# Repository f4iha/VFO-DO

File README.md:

# VFO-DO RF Generator

This VFO-DO is a HF generator covering from few kHz to 100MHz. This project provide to any beginner in electronic or radio the necessary elements to build a source of stable frequency (precise at the Herz level due to the steering by a GPS)... and it is very simple to build.

It is coming from the initial idea from Gene Marcus W3PM/GM4YRE and published in an [article](http://www.arrl.org/files/file/QEX_Next_Issue/2015/Jul-Aug_2015/Marcus.pdf) of QEX.
This repository is an evolution of the work done by F6ITU who provided a [KiCad project](https://github.com/F6ITU/VFO-DO/) for this VFO-DO.

This project can be used as field equipements, where it is unthinkable to move a served oscillator (fragile and expensive). This is mainly a simple approach to drive a little SDR or replace the VFO of a traditional radio device.

The cost of this is around 30 euros. However, please take in account the phase noise of this type of generator cannot compete with a traditional VFO-DO

## Specific features

During the integration, few changes were applied in the initial code of the author:
  * usage of a I2C Crystal Display, it is freeing multiple pin on the Arduino
  * add a button to disable the GPS at start

## Intellectual property and licence

The intellectual property and the publishing rights are owned respectively by the author and the publishing society mentioned.

Permission is granted to use, copy, modify, and distribute this firmware and documentation for non-commercial purposes.

## External links

More informations on the oscillator module based on SiLabs Si5351 : 
[https://learn.adafruit.com/adafruit-si5351-clock-generator-breakout?view=all](https://learn.adafruit.com/adafruit-si5351-clock-generator-breakout?view=all)

Another source for this module 
[https://www.sv1afn.com/si5351a.html](https://www.sv1afn.com/si5351a.html)
Careful : this last module is not "pin compatible" with the previous one

Origin firmware from the author [http://www.knology.net/~gmarcus/Si5351/Si5351_vfo_v5.ino.zip](http://www.knology.net/~gmarcus/Si5351/Si5351_vfo_v5.ino.zip)

A WSPR emitter-receiver designed by the author and using the VFO-DO
[http://www.knology.net/~gmarcus/Si5351/Si5351A_WSPR_XCVR.pdf](http://www.knology.net/~gmarcus/Si5351/Si5351A_WSPR_XCVR.pdf)

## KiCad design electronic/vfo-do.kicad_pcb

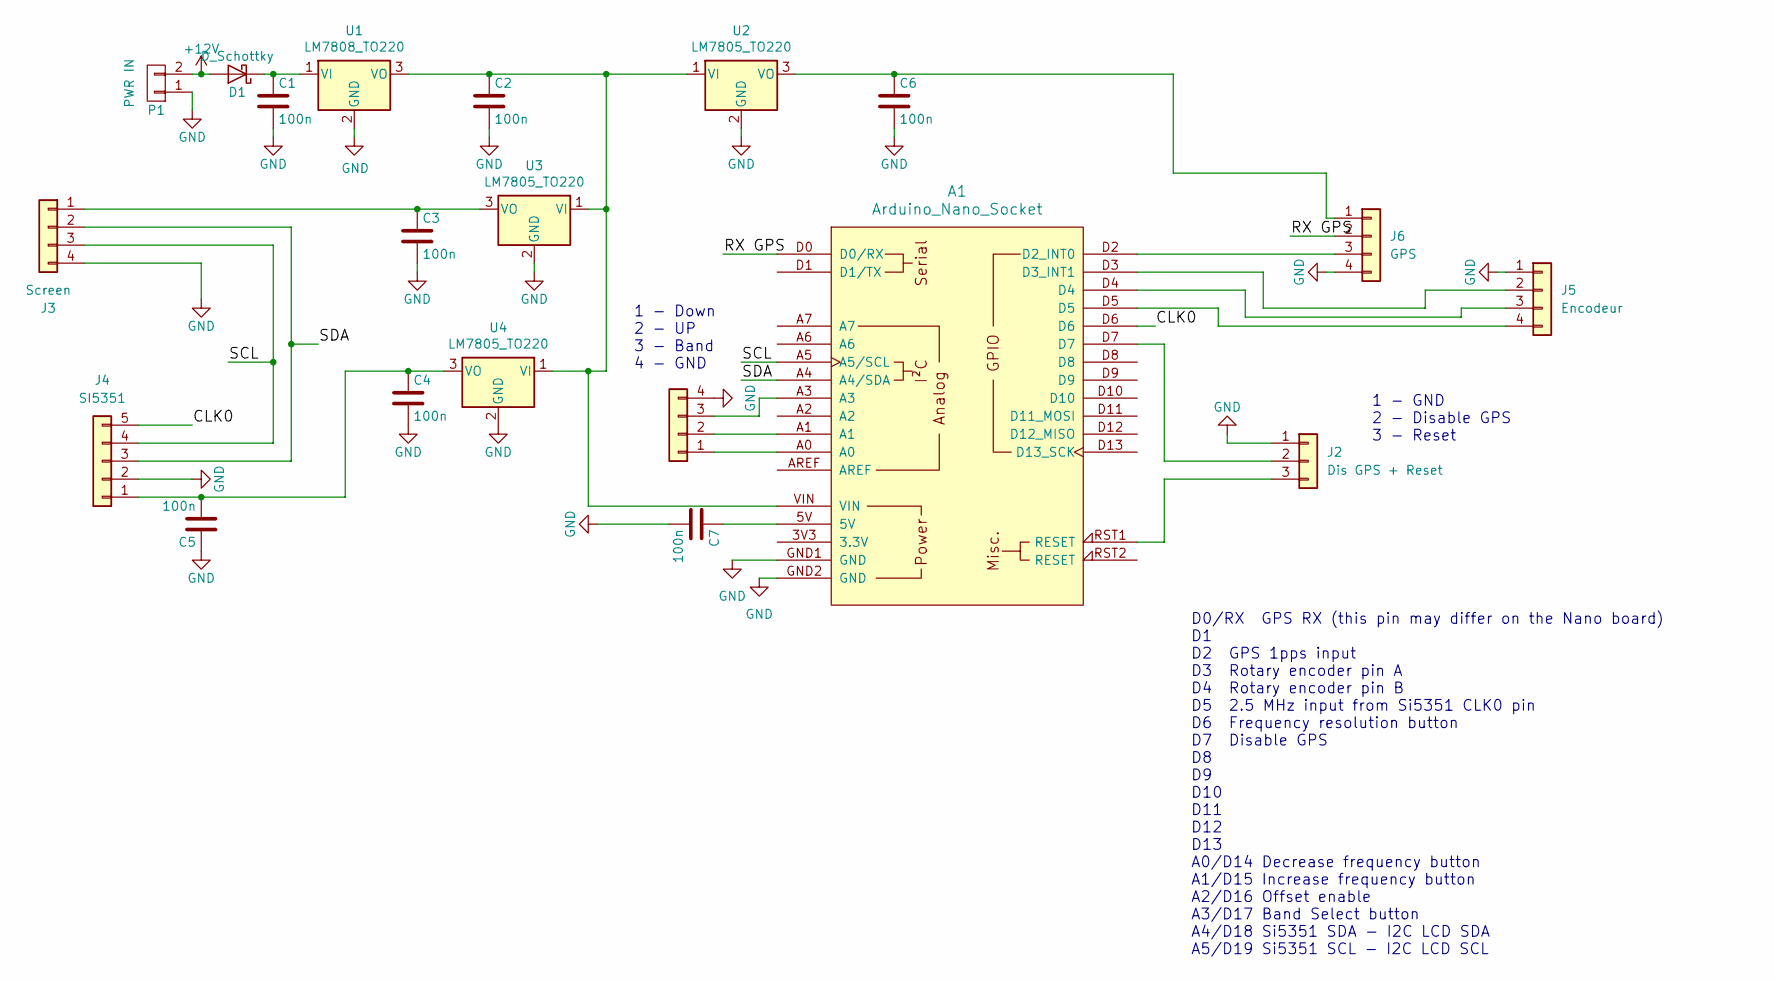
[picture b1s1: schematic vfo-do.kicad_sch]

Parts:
A1: Arduino_Nano_Socket
C1, C2, C3, C4, C5, C6, C7: 100n; C_Disc_D5.0mm_W2.5mm_P5.00mm
D1: D_Schottky; D_DO-41_SOD81_P7.62mm_Horizontal
J1: Commands; Molex_KK-254_AE-6410-04A_1x04_P2.54mm_Vertical
J2: Dis GPS + Reset; Molex_KK-254_AE-6410-03A_1x03_P2.54mm_Vertical
J3: Screen; Molex_KK-254_AE-6410-04A_1x04_P2.54mm_Vertical
J4: SI5351; Molex_KK-254_AE-6410-05A_1x05_P2.54mm_Vertical
J5: Encodeur; Molex_KK-254_AE-6410-04A_1x04_P2.54mm_Vertical
J6: GPS; Molex_KK-254_AE-6410-04A_1x04_P2.54mm_Vertical
P1: PWR IN; Molex_KK-254_AE-6410-02A_1x02_P2.54mm_Vertical
U1: LM7808_TO220; TO-220-3_Vertical
U2, U3, U4: LM7805_TO220; TO-220-3_Vertical

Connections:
+12V: D1.2 (A), P1.2
/CLK0: A1.D6, J4.5
/RX GPS: A1.D0 (D0/RX), J6.2
/SCL: A1.A5 (A5/SCL), J3.3, J4.4
/SDA: A1.A4 (A4/SDA), J3.2, J4.3
GND: A1.GND1 (GND), A1.GND2 (GND), C1.2, C2.2, C3.2, C4.2, C5.1, C6.2, C7.2, J1.4, J2.1, J3.4, J4.2, J5.1, J6.4, P1.1, U1.2 (GND), U2.2 (GND), U3.2 (GND), U4.2 (GND)
unnamed: A1.D2 (D2_INT0), J6.3
unnamed: A1.D3 (D3_INT1), J5.2
unnamed: A1.5V, C7.1
unnamed: C1.1, D1.1 (K), U1.1 (VI)
unnamed: A1.A0, J1.1
unnamed: A1.A1, J1.2
unnamed: A1.A3, J1.3
unnamed: A1.D7, J2.2
unnamed: A1.RST1 (RESET), J2.3
unnamed: C3.1, J3.1, U3.3 (VO)
unnamed: C4.1, C5.2, J4.1, U4.3 (VO)
unnamed: A1.D4, J5.3
unnamed: A1.D5, J5.4
unnamed: C6.1, J6.1, U2.3 (VO)
unnamed: A1.VIN, C2.1, U1.3 (VO), U2.1 (VI), U3.1 (VI), U4.1 (VI)

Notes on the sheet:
1 - Down 2 - UP 3 - Band 4 - GND
D0/RX GPS RX (this pin may differ on the Nano board) D1 D2 GPS 1pps input D3 Rotary encoder pin A D4 Rotary encoder pin B D5 2.5 MHz input from Si5351 CLK0 pin D6 Frequency resolution button D7 Disable GPS D8 D9 D10 D11 D12 D13 A0/D14 Decrease frequency button A1/D15 Increase frequency button A2/D1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
1 - GND 2 - Disable GPS 3 - Reset

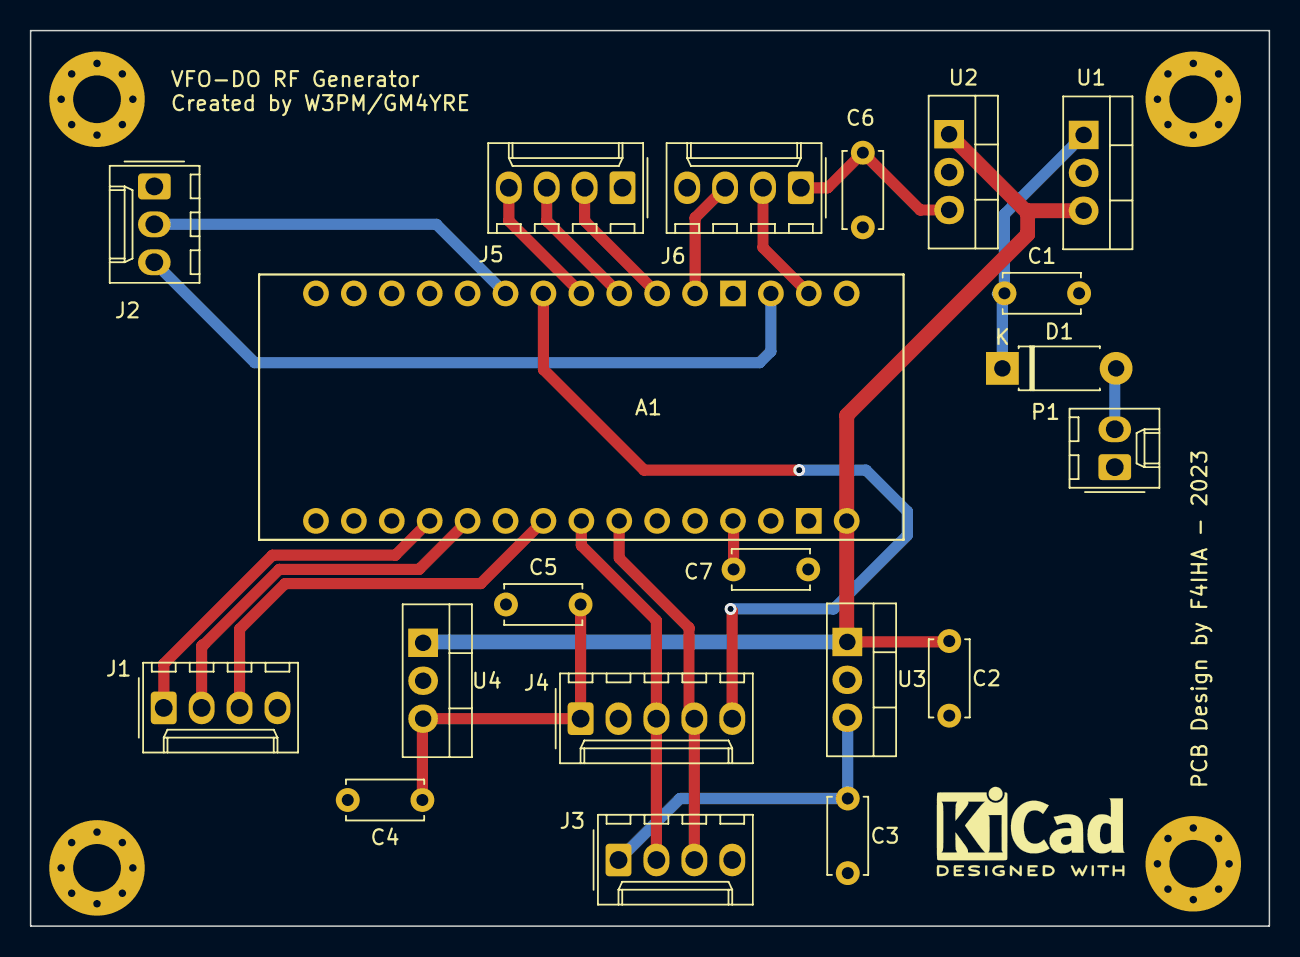
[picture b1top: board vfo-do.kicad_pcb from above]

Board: 2 copper layers, 83.0 x 60.0 mm, 20 parts (0 on the bottom side), 21 nets.

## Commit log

2021-06-25 Commit initial
2021-06-25 Switching screen to I2C support
2021-06-25 Fix compilation error and add button to disable GPS at start
2021-07-02 Complete README with all initial informations
2021-09-13 Add GPS switchoff button
2021-12-27 Migrate Kicad5 to Kicad6
2021-12-27 Migration Kicad5 to Kicad6
2024-01-05 electronics changes for PCB
2024-01-05 Firmware pin adjustments for PCB
2024-01-05 Gerber files
2024-01-05 Rename gerber to pcb folder
